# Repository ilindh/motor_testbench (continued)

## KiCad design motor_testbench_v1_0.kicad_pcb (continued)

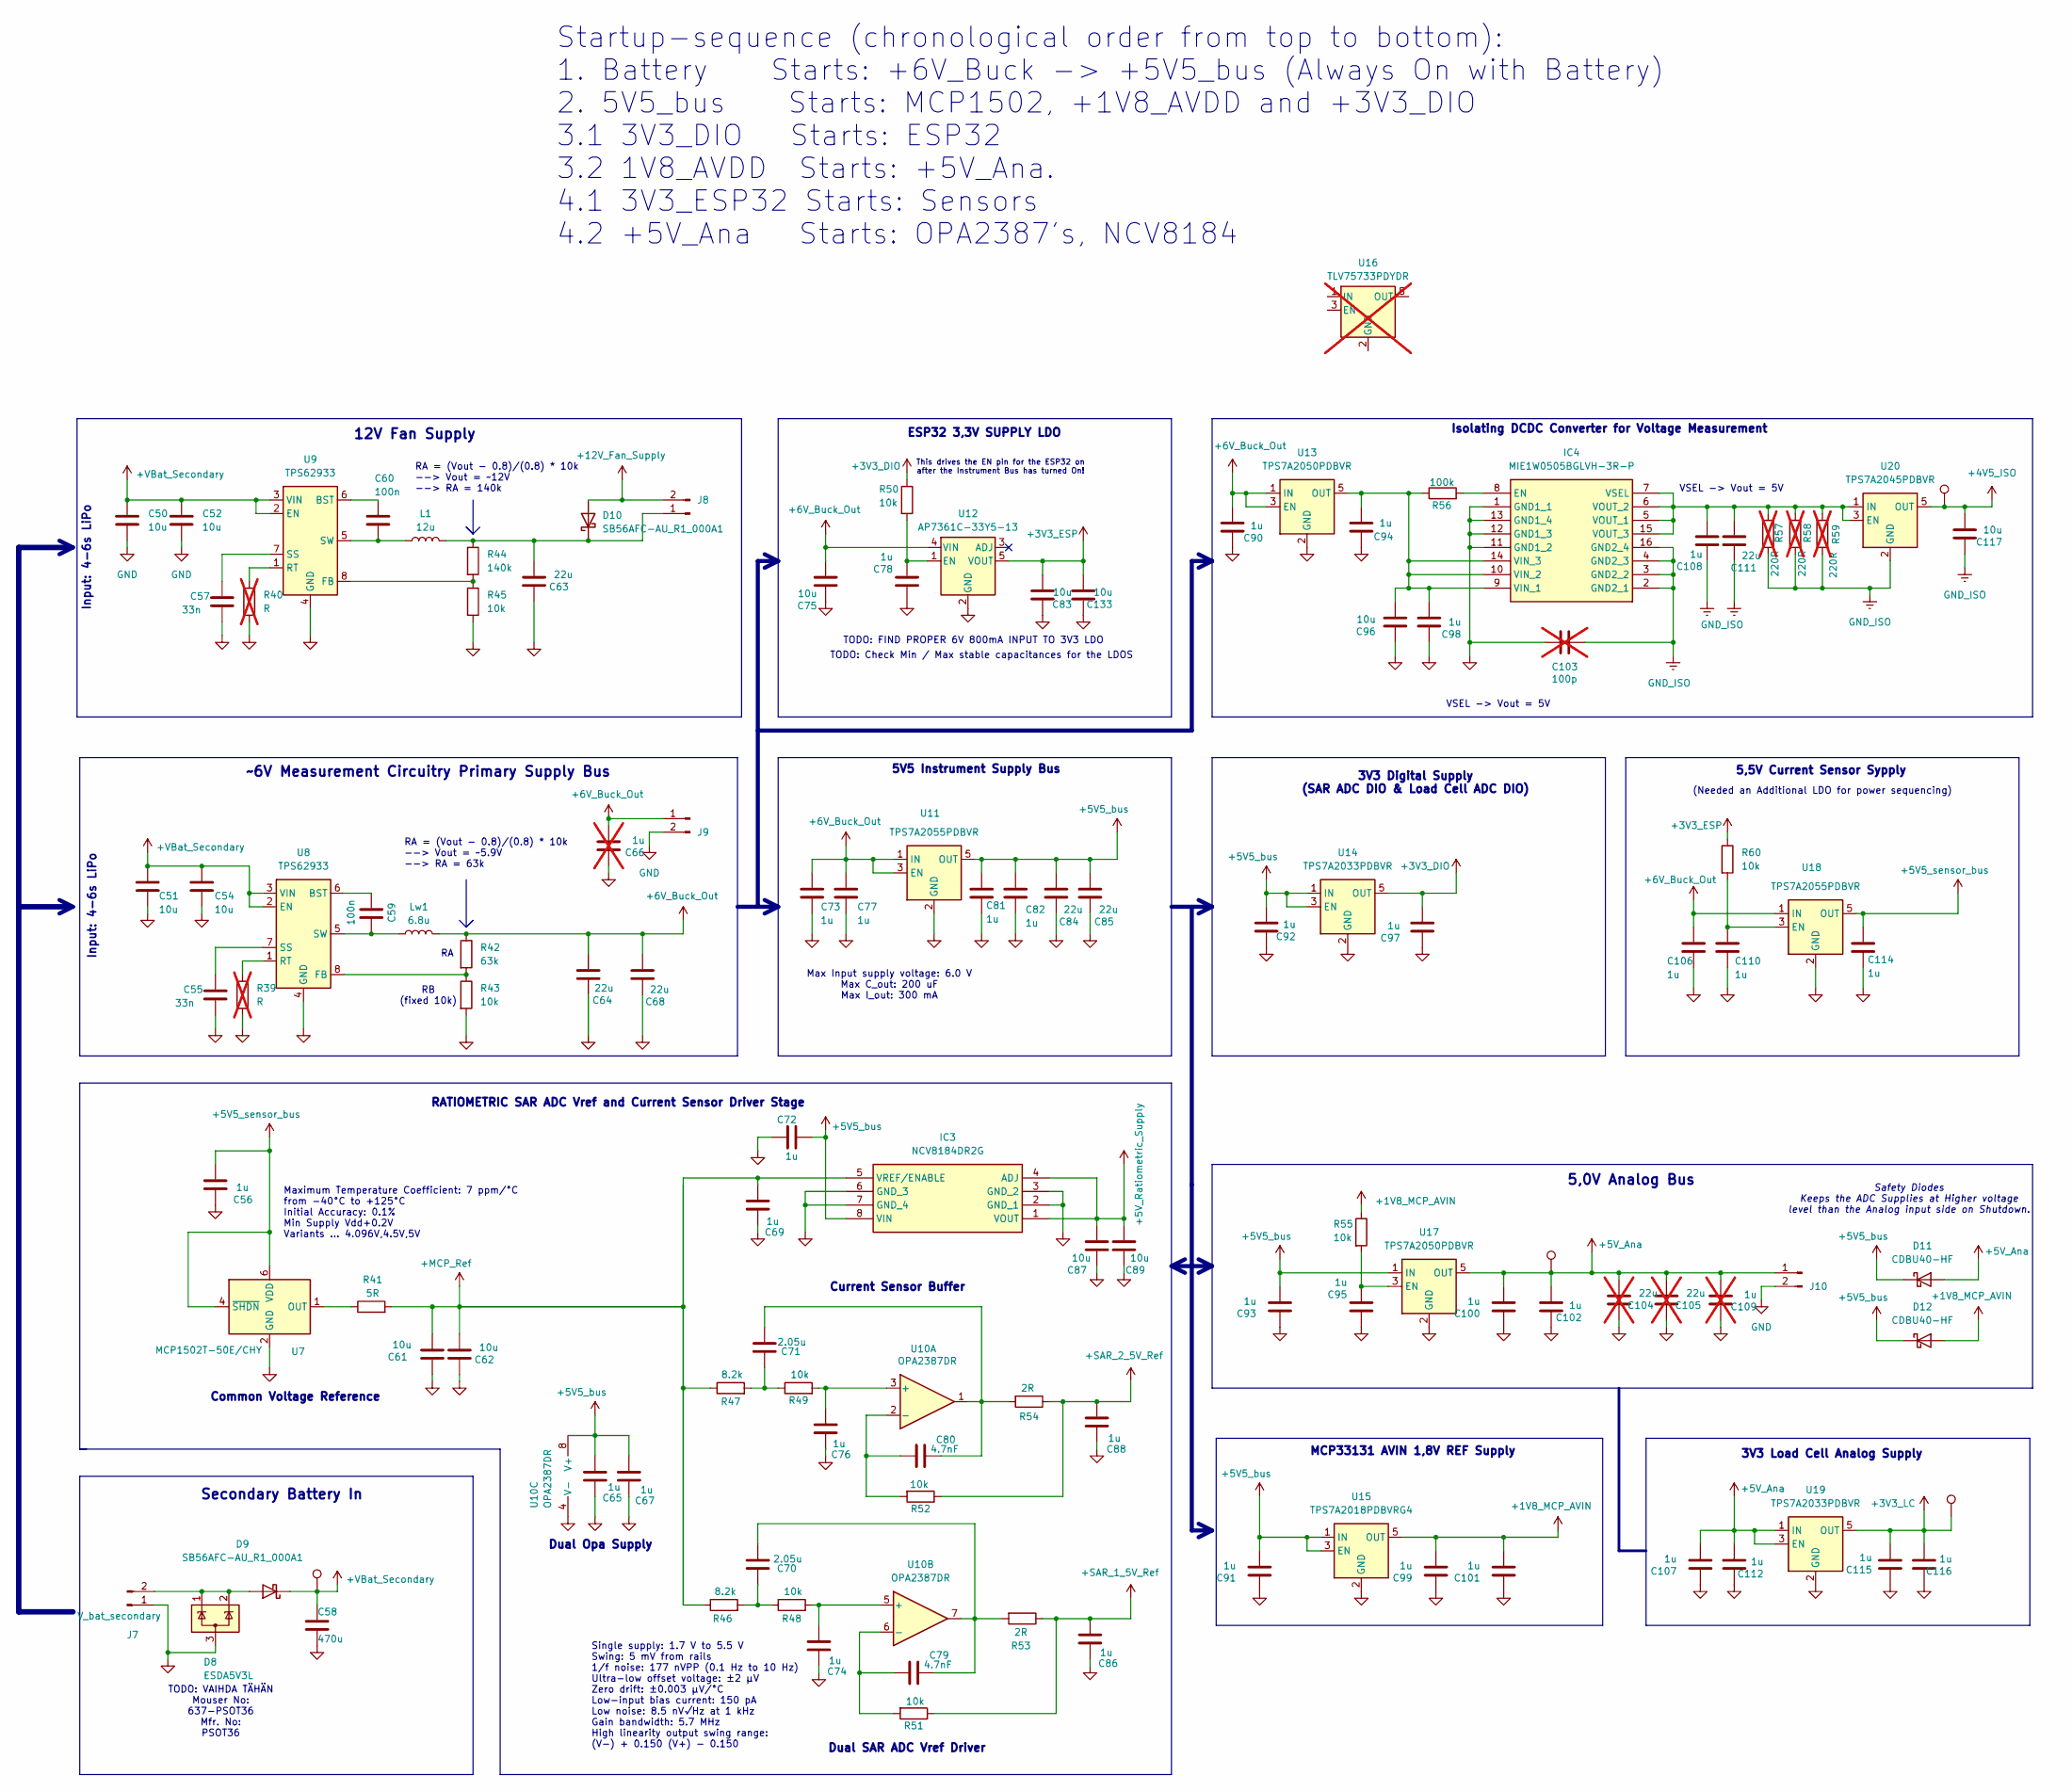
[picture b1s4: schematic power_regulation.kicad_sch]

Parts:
C50, C51, C52, C54, C61, C62, C75, C83, C87, C89, C96, C117, C133: 10u; C_0603_1608Metric_Pad1.08x0.95mm_HandSolder
C55, C57: 33n; C_0603_1608Metric_Pad1.08x0.95mm_HandSolder
C56, C65, C67, C69, C72, C73, C74, C76, C77, C78, C81, C82, C86, C88, C90, C91, C92, C93, C94, C95, C97, C98, C99, C100, C101, C102, C106, C107, C108, C110, C112, C114, C115, C116: 1u; C_0603_1608Metric_Pad1.08x0.95mm_HandSolder
C58: 470u; CP_Elec_6.3x5.3
C59, C60: 100n; C_0603_1608Metric_Pad1.08x0.95mm_HandSolder
C63, C64, C68, C84, C85, C111: 22u; C_1206_3216Metric_Pad1.33x1.80mm_HandSolder
C66, C109: 1u; C_0603_1608Metric_Pad1.08x0.95mm_HandSolder; not fitted
C70, C71: 2.05u; C_0603_1608Metric_Pad1.08x0.95mm_HandSolder
C79, C80: 4.7nF; C_0603_1608Metric_Pad1.08x0.95mm_HandSolder
C103: 100p; C_0603_1608Metric_Pad1.08x0.95mm_HandSolder; not fitted
C104, C105: 22u; C_1206_3216Metric_Pad1.33x1.80mm_HandSolder; not fitted
D8: ESDA5V3L; SOT-23-3
D9, D10: SB56AFC-AU_R1_000A1; D_SMA
D11, D12: CDBU40-HF; D_0603_1608Metric
DIO1: TestPoint; TestPoint_Pad_D1.0mm
IC3: NCV8184DR2G; SOIC127P600X175-8N; Manufacturer_Part_Number NCV8184DR2G; Mouser Part Number 863-NCV8184DR2G
IC4: MIE1W0505BGLVH-3R-P; MIE1W0505BGLVH3RP; Manufacturer_Part_Number MIE1W0505BGLVH-3R-P; Mouser Part Number 946-MIE1W0505BGLVH3P
IN1: TestPoint; TestPoint_Pad_D1.0mm
J7: V_bat_secondary; AMASS_XT60PW-M_1x02_P7.20mm_Horizontal_with3DModel
J8, J9, J10: Conn_01x02_Pin; PinHeader_1x02_P2.54mm_Vertical
L1: 12u; L_1206_3216Metric_Pad1.42x1.75mm_HandSolder
Lw1: 6.8u; L_1206_3216Metric_Pad1.42x1.75mm_HandSolder
R39, R40: R; R_0603_1608Metric_Pad0.98x0.95mm_HandSolder; not fitted
R41: 5R; R_0603_1608Metric_Pad0.98x0.95mm_HandSolder
R42: 63k; R_0603_1608Metric_Pad0.98x0.95mm_HandSolder
R43, R45, R48, R49, R50, R51, R52, R55, R60: 10k; R_0603_1608Metric_Pad0.98x0.95mm_HandSolder
R44: 140k; R_0603_1608Metric_Pad0.98x0.95mm_HandSolder
R46, R47: 8.2k; R_0603_1608Metric_Pad0.98x0.95mm_HandSolder
R53, R54: 2R; R_0603_1608Metric_Pad0.98x0.95mm_HandSolder
R56: 100k; R_0603_1608Metric_Pad0.98x0.95mm_HandSolder
R57, R58, R59: 220R; R_0603_1608Metric_Pad0.98x0.95mm_HandSolder; not fitted
U7: MCP1502T-50E/CHY; SOT-23-6
U8, U9: TPS62933; SOT-583-8
U10: OPA2387DR; SOIC-8_3.9x4.9mm_P1.27mm
U11, U18: TPS7A2055PDBVR; SOT-23-5; Mouser_nro 595-TPS7A2055PDBVR
U12: AP7361C-33Y5-13; SOT-89-5_Handsoldering
U13, U17: TPS7A2050PDBVR; SOT-23-5
U14, U19: TPS7A2033PDBVR; SOT-23-5
U15: TPS7A2018PDBVRG4; SOT-23-5
U16: TLV75733PDYDR; SOT-23-5; not fitted
U20: TPS7A2045PDBVR; SOT-23-5
Vref1, Vref2: TestPoint; TestPoint_Pad_D1.0mm

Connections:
+1V8_MCP_AVIN: C99.2, C101.2, D12.2 (A), R55.1, U15.5 (OUT); also elsewhere on the board
+3V3_DIO: C97.2, R50.1, U14.5 (OUT); also elsewhere on the board
+3V3_ESP: C83.2, C133.2, R60.1, U12.5 (VOUT); also elsewhere on the board
+3V3_LC: C115.2, C116.2, DIO1.1 (1_1), U19.5 (OUT); also elsewhere on the board
+4V5_ISO: C117.2, U20.5 (OUT), Vref2.1 (1_1); also elsewhere on the board
+5V5_bus: C65.2, C67.2, C72.2, C81.1, C82.1, C84.2, C85.2, C91.2, C92.2, C93.2, D11.1 (K), D12.1 (K), IC3.8 (VIN), U10.8 (V+), U11.5 (OUT), U14.1 (IN), U14.3 (EN), U15.1 (IN), U15.3 (EN), U17.1 (IN); also elsewhere on the board
+5V5_sensor_bus: C56.2, C114.1, U7.4 (~SHDN), U7.6 (VDD), U18.5 (OUT)
+5V_Ana: C100.2, C102.2, C104.2, C105.2, C107.2, C109.2, C112.2, D11.2 (A), J10.1, U17.5 (OUT), U19.1 (IN), U19.3 (EN), Vref1.1 (1_1); also elsewhere on the board
+5V_Ratiometric_Supply: C87.2, C89.2, IC3.1 (VOUT), IC3.4 (ADJ); also elsewhere on the board
+6V_Buck_Out: C64.2, C66.2, C68.2, C73.1, C75.2, C77.1, C90.2, C106.1, J9.1, Lw1.2, R42.1, U11.1 (IN), U11.3 (EN), U12.4 (VIN), U13.1 (IN), U13.3 (EN), U18.1 (IN)
+12V_Fan_Supply: D10.2 (A), J8.2; also elsewhere on the board
+MCP_Ref: C61.2, C62.2, C69.2, IC3.5 (VREF/ENABLE), R41.2, R46.1, R47.1
+SAR_1_5V_Ref: C86.2, R51.1, R53.1; also elsewhere on the board
+SAR_2_5V_Ref: C88.2, R52.1, R54.1; also elsewhere on the board
+VBat_Secondary: C50.1, C51.1, C52.1, C54.1, C58.1, D9.1 (K), IN1.1 (1_1), U8.2 (EN), U8.3 (VIN), U9.2 (EN), U9.3 (VIN); also elsewhere on the board
GND: C50.2, C51.2, C52.2, C54.2, C55.2, C56.1, C57.2, C58.2, C61.1, C62.1, C63.1, C64.1, C65.1, C66.1, C67.1, C68.1, C69.1, C72.1, C73.2, C74.1, C75.1, C76.1, C77.2, C78.1, C81.2, C82.2, C83.1, C84.1, C85.1, C86.1, C87.1, C88.1, C89.1, C90.1, C91.1, C92.1, C93.1, C94.1, C95.1, C96.1, C97.1, C98.1, C99.1, C100.1, C101.1, C102.1, C103.2, C104.1, C105.1, C106.2, C107.1, C109.1, C110.2, C112.1, C114.2, C115.1, C116.1, C133.1, D8.3 (A), IC3.2 (GND_1), IC3.3 (GND_2), IC3.6 (GND_3), IC3.7 (GND_4), IC4.1 (GND1_1), IC4.11 (GND1_2), IC4.12 (GND1_3), IC4.13 (GND1_4), J7.1, J9.2, J10.2, R39.2, R40.2, R43.2, R45.2, U7.2 (GND), U7.3 (GND), U7.5 (GND), U8.4 (GND), U9.4 (GND), U10.4 (V-), U11.2 (GND), U12.2 (GND), U13.2 (GND), U14.2 (GND), U15.2 (GND), U17.2 (GND), U18.2 (GND), U19.2 (GND); also elsewhere on the board
GND_ISO: C103.1, C108.1, C111.1, C117.1, IC4.2 (GND2_1), IC4.3 (GND2_2), IC4.4 (GND2_3), IC4.16 (GND2_4), R57.2, R58.2, R59.2, U20.2 (GND); also elsewhere on the board
unnamed: C70.1, R46.2, R48.1
unnamed: C70.2, C79.2, R53.2, U10.7
unnamed: C71.1, R47.2, R49.1
unnamed: C71.2, C80.2, R54.2, U10.1
unnamed: D8.1 (K), D8.2 (K), D9.2 (A), J7.2
unnamed: C63.2, D10.1 (K), J8.1, L1.2, R44.1
unnamed: IC4.8 (EN), R56.2
unnamed: C94.2, C96.2, C98.2, IC4.9 (VIN_1), IC4.10 (VIN_2), IC4.14 (VIN_3), R56.1, U13.5 (OUT)
unnamed: C108.2, C111.2, IC4.5 (VOUT_1), IC4.6 (VOUT_2), IC4.7 (VSEL), IC4.15 (VOUT_3), R57.1, R58.1, R59.1, U20.1 (IN), U20.3 (EN)
unnamed: R41.1, U7.1 (OUT)
unnamed: C59.1, U8.6 (BST)
unnamed: R42.2, R43.1, U8.8 (FB)
unnamed: R39.1, U8.1 (RT)
unnamed: C55.1, U8.7 (SS)
unnamed: C59.2, Lw1.1, U8.5 (SW)
unnamed: C60.1, U9.6 (BST)
unnamed: R44.2, R45.1, U9.8 (FB)
unnamed: R40.1, U9.1 (RT)
unnamed: C57.1, U9.7 (SS)
unnamed: C60.2, L1.1, U9.5 (SW)
unnamed: C76.2, R49.2, U10.3 (+)
unnamed: C80.1, R52.2, U10.2 (-)
unnamed: C74.2, R48.2, U10.5 (+)
unnamed: C79.1, R51.2, U10.6 (-)
unnamed: C78.2, R50.2, U12.1 (EN)
unnamed: C95.2, R55.2, U17.3 (EN)
unnamed: C110.1, R60.2, U18.3 (EN)

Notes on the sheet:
Safety Diodes Keeps the ADC Supplies at Higher voltage level than the Analog input side on Shutdown.
Dual Opa Supply
ESP32 3,3V SUPPLY LDO
Max Input supply voltage: 6.0 V Max C_out: 200 uF Max I_out: 300 mA
TODO: VAIHDA TÄHÄN Mouser No: 637-PSOT36 Mfr. No: PSOT36
(Needed an Additional LDO for power sequencing)
This drives the EN pin for the ESP32 on after the Instrument Bus has turned On!
TODO: Check Min / Max stable capacitances for the LDOS
RATIOMETRIC SAR ADC Vref and Current Sensor Driver Stage
RA = (Vout - 0.8)/(0.8) * 10k --> Vout = ~12V --> RA = 140k
MCP33131 AVIN 1,8V REF Supply
Input: 4-6s LiPo
Startup-sequence (chronological order from top to bottom): 1. Battery Starts: +6V_Buck -> +5V5_bus (Always On with Battery) 2. 5V5_bus Starts: MCP1502, +1V8_AVDD and +3V3_DIO 3.1 3V3_DIO Starts: ESP32 3.2 1V8_AVDD Starts: +5V_Ana. 4.1 3V3_ESP32 Starts: Sensors 4.2 +5V_Ana Starts: OPA2387's, NCV8184
5,5V Current Sensor Sypply
12V Fan Supply
Dual SAR ADC Vref Driver
RA = (Vout - 0.8)/(0.8) * 10k --> Vout = ~5.9V --> RA = 63k
Single supply: 1.7 V to 5.5 V Swing: 5 mV from rails 1/f noise: 177 nVPP (0.1 Hz to 10 Hz) Ultra-low offset voltage: ±2 µV Zero drift: ±0.003 µV/°C Low-input bias current: 150 pA Low noise: 8.5 nV√Hz at 1 kHz Gain bandwidth: 5.7 MHz High linearity output swing range: (V-) + 0.150 (V+) - 0.150
Current Sensor Buffer
RB (fixed 10k)
5,0V Analog Bus
VSEL -> Vout = 5V
5V5 Instrument Supply Bus
Common Voltage Reference
Secondary Battery In
Maximum Temperature Coefficient: 7 ppm/°C from -40°C to +125°C Initial Accuracy: 0.1% Min Supply Vdd+0.2V Variants ... 4.096V,4.5V,5V
3V3 Digital Supply (SAR ADC DIO & Load Cell ADC DIO)
Isolating DCDC Converter for Voltage Measurement
TODO: FIND PROPER 6V 800mA INPUT TO 3V3 LDO
~6V Measurement Circuitry Primary Supply Bus
3V3 Load Cell Analog Supply

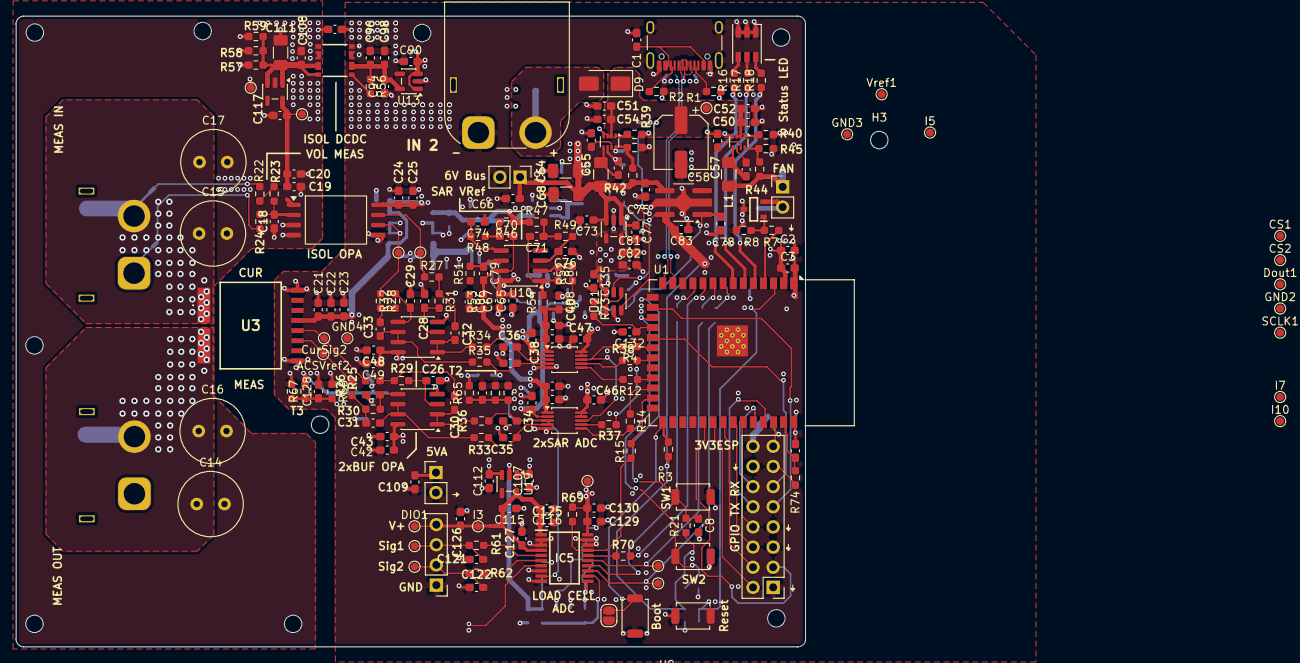
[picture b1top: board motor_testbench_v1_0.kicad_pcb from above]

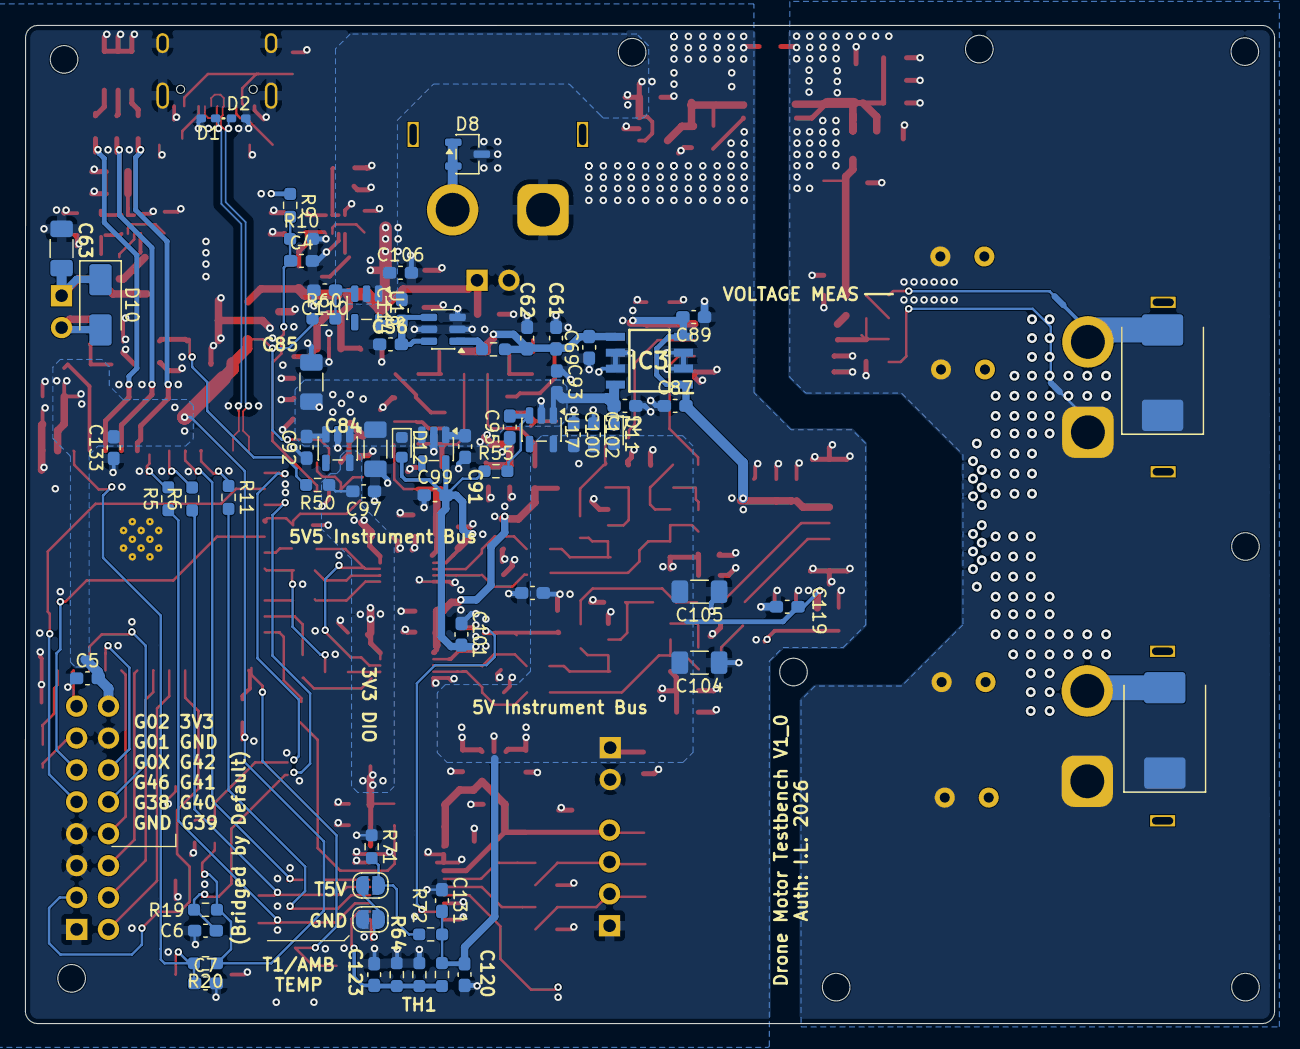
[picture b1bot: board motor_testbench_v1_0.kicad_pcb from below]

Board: 4 copper layers, 99.5 x 79.5 mm, 296 parts (68 on the bottom side), 130 nets.

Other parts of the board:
ACSVref2: TestPoint; TestPoint_Pad_D1.0mm
CurSig2: TestPoint; TestPoint_Pad_D1.0mm

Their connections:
/Voltage and Current Measurements/ACS_VREF: ACSVref2.1 (1_1); also elsewhere on the board
/Voltage and Current Measurements/cur_sig: CurSig2.1 (1_1); also elsewhere on the board

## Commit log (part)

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2026-03-29 Initial commit.
    [KiCad Version: 9.0.8]
2026-04-01 Improved layout, added TVS diodes. Rotated ESP32, Changed proper SPI pins, finalized the load cell module area.
    [KiCad Version: 9.0.8]
2026-04-01 Moved the 1V8 Ref to bottom side of the board. Improved layout slightly / moved the Vref IC further away from hot / noisy side / further away from the noisy DCDC. Also managed to route the 1V8 and SP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
    [KiCad Version: 9.0.8]
2026-04-03 Shortened high current path / improved the high current side layout.
    [KiCad Version: 9.0.8]
2026-04-09 Improved layout.
    [KiCad Version: 9.0.8]
2026-04-09 Minor tweaks.
    [KiCad Version: 9.0.8]
2026-04-29 testi
    [KiCad Version: 9.0.7]
2026-04-29 Testi2
    [KiCad Version: 9.0.7]
2026-04-29 Pientä parantelua
    [KiCad Version: 9.0.7]
2026-06-18 Add proper Load Cell ADC. Improve everything. Almost ready.
    [KiCad Version: 9.0.8]
2026-06-26 Switched isolating opamp. Switched Isolating DCDC converter. Minor layout improvements. Added load cell ADC.
    [KiCad Version: 10.0.4]
2026-06-27 Implemented proper sallen key filter. Add 4V2 LDO Back.
    [KiCad Version: 10.0.4]
2026-06-27 add buttons. Minor tweaks.
    [KiCad Version: 10.0.4]
2026-06-28 Quite final version with ACS current sensor.
    [KiCad Version: 10.0.4]
2026-06-28 Start adding new current sensor
    [KiCad Version: 10.0.4]
